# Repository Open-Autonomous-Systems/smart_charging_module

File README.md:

# smart_charging_module
open source hardware design and recorded software to be used for intelligently charge robotic platforms like UAVs, etc using low power energy sources. This repo contains ECAD source files and gerber file of the V1 of the project.

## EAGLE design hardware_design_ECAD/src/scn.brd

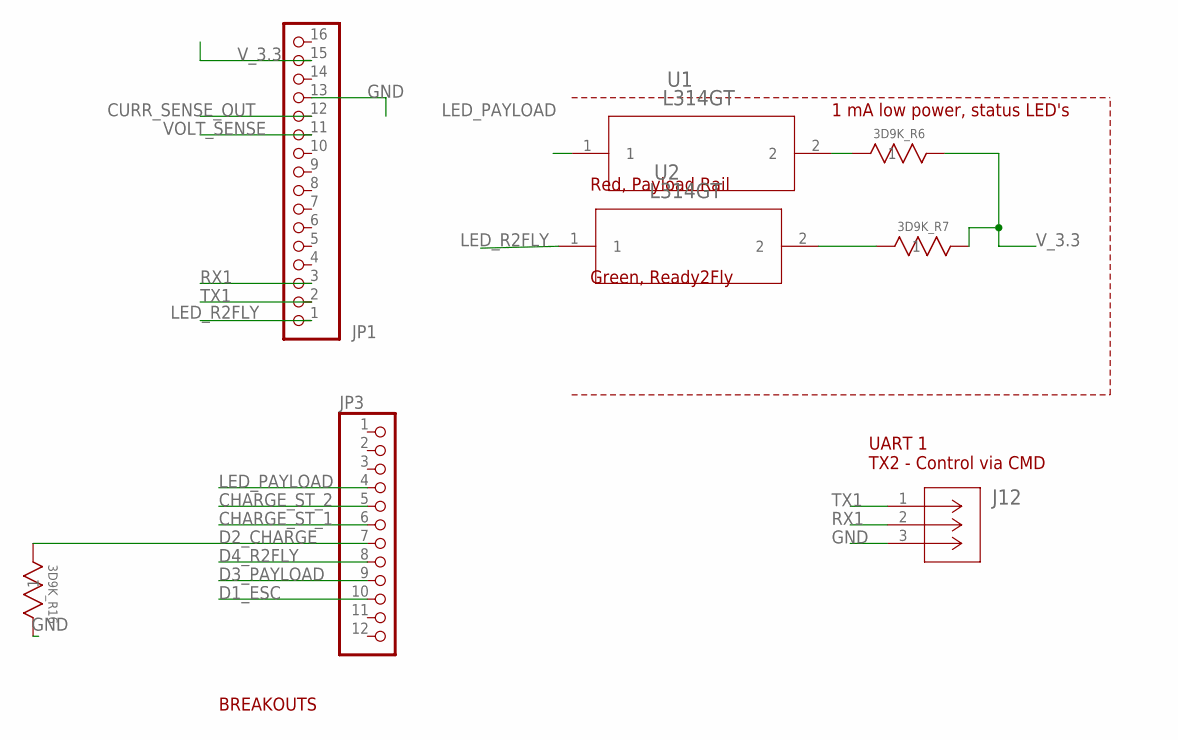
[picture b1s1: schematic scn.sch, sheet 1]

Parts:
3D9K_R6, 3D9K_R7, 3D9K_R16: CF14JT10K0; STA_CF14_STP
J12: B03B-PASK(LF)(SN); CONN_B03B-PASK_JST
JP1: HEADER-1X16ROUND; 1X16_ROUND
JP3: HEADER-1X12; 1X12_ROUND
U1, U2: L314GT; L314GT_AOP

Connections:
CHARGE_ST_1: JP3.6; also elsewhere on the board
CHARGE_ST_2: JP3.5; also elsewhere on the board
CURR_SENSE_OUT: JP1.12; also elsewhere on the board
D1_ESC: JP3.10; also elsewhere on the board
D2_CHARGE: 3D9K_R16.1, JP3.7; also elsewhere on the board
D3_PAYLOAD: JP3.9; also elsewhere on the board
D4_R2FLY: JP3.8
GND: 3D9K_R16.2, J12.3, JP1.13; also elsewhere on the board
LED_PAYLOAD: JP3.4, U1.1
LED_R2FLY: JP1.1, U2.1
unnamed: 3D9K_R6.1, U1.2
unnamed: 3D9K_R7.1, U2.2
RX1: J12.2, JP1.3
TX1: J12.1, JP1.2
VOLT_SENSE: JP1.11
V_3.3: 3D9K_R6.2, 3D9K_R7.2, JP1.15; also elsewhere on the board

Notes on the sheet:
BREAKOUTS
Red, Payload Rail
Green, Ready2Fly
1 mA low power, status LED's
UART 1 TX2 - Control via CMD

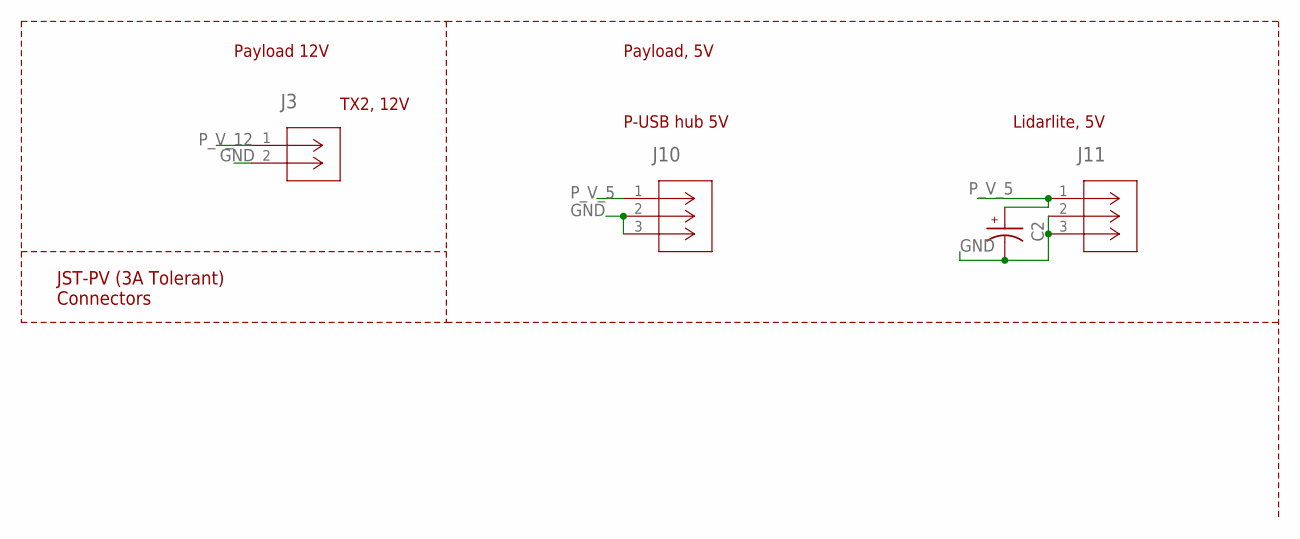
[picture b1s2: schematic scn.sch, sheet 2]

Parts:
C2: ECA1CM471; CAPPRD350W60D800H1150
J3: B02B-PASK(LF)(SN); CONN_B02B-PASK(LF)(SN)_JST
J10, J11: B03B-PASK(LF)(SN); CONN_B03B-PASK_JST

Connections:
GND: C2.N, J3.2, J10.2, J10.3, J11.2, J11.3; also elsewhere on the board
P_V_5: C2.P, J10.1, J11.1; also elsewhere on the board
P_V_12: J3.1; also elsewhere on the board

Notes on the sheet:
Payload 12V
Payload, 5V
TX2, 12V
Lidarlite, 5V
P-USB hub 5V
JST-PV (3A Tolerant) Connectors

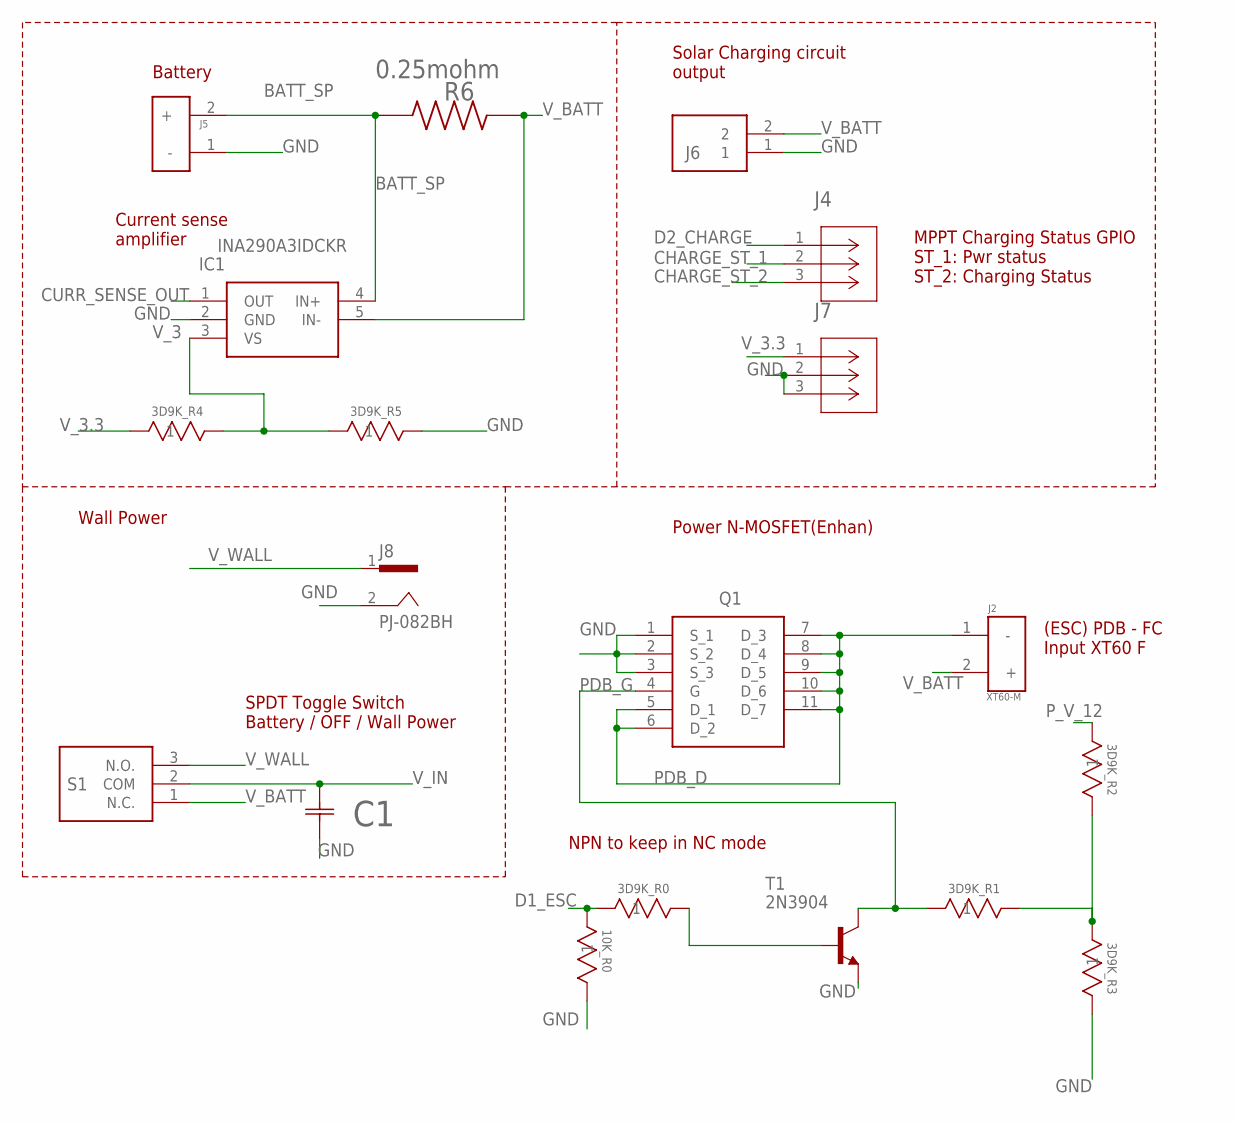
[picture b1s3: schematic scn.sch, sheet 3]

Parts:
3D9K_R0, 3D9K_R1, 3D9K_R2, 3D9K_R3, 3D9K_R4, 3D9K_R5, 10K_R0: CF14JT10K0; STA_CF14_STP
C1: 25PX1000MEFCT810X16; CAP_PK/PZ_10X16_LOW_RUB
IC1: INA290A3IDCKR; SOT65P210X110-5N
J2, J5: XT60-M; AMASS_XT60-M
J4, J7: B03B-PASK(LF)(SN); CONN_B03B-PASK_JST
J6: XT30UPB-M; SHDR2W160P0X500_1X2_1020X520X1
J8: PJ-082BH; CUI_PJ-082BH
Q1: SIRA50DP-T1-RE3; SI7852ADPT1GE3
R6: 0.25mohm; RESC6864X124N
S1: 48ASSP3S1M2QBT
T1: 2N3904; TO92

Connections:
BATT_SP: IC1.4 (IN+), J5.2 (+), R6.1
CHARGE_ST_1: J4.2; also elsewhere on the board
CHARGE_ST_2: J4.3; also elsewhere on the board
CURR_SENSE_OUT: IC1.1 (OUT); also elsewhere on the board
D1_ESC: 3D9K_R0.1, 10K_R0.1; also elsewhere on the board
D2_CHARGE: J4.1; also elsewhere on the board
GND: 3D9K_R3.2, 3D9K_R5.2, 10K_R0.2, C1.2, IC1.2 (GND), J5.1 (-), J6.1, J7.2, J7.3, J8.2, Q1.1 (S_1), Q1.2 (S_2), Q1.3 (S_3), T1.3 (E); also elsewhere on the board
unnamed: 3D9K_R1.2, 3D9K_R2.2, 3D9K_R3.1
unnamed: 3D9K_R0.2, T1.2 (B)
PDB_D: J2.1 (-), Q1.5 (D_1), Q1.6 (D_2), Q1.7 (D_3), Q1.8 (D_4), Q1.9 (D_5), Q1.10 (D_6), Q1.11 (D_7)
PDB_G: 3D9K_R1.1, Q1.4 (G), T1.1 (C)
P_V_12: 3D9K_R2.1; also elsewhere on the board
V_3: 3D9K_R4.2, 3D9K_R5.1, IC1.3 (VS)
V_3.3: 3D9K_R4.1, J7.1; also elsewhere on the board
V_BATT: IC1.5 (IN-), J2.2 (+), J6.2, R6.2, S1.1 (N.C.)
V_IN: C1.1, S1.2 (COM); also elsewhere on the board
V_WALL: J8.1, S1.3 (N.O.)

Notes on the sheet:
Current sense amplifier
Battery
Solar Charging circuit output
(ESC) PDB - FC Input XT60 F
Wall Power
SPDT Toggle Switch Battery / OFF / Wall Power
Power N-MOSFET(Enhan)
NPN to keep in NC mode
MPPT Charging Status GPIO ST_1: Pwr status ST_2: Charging Status

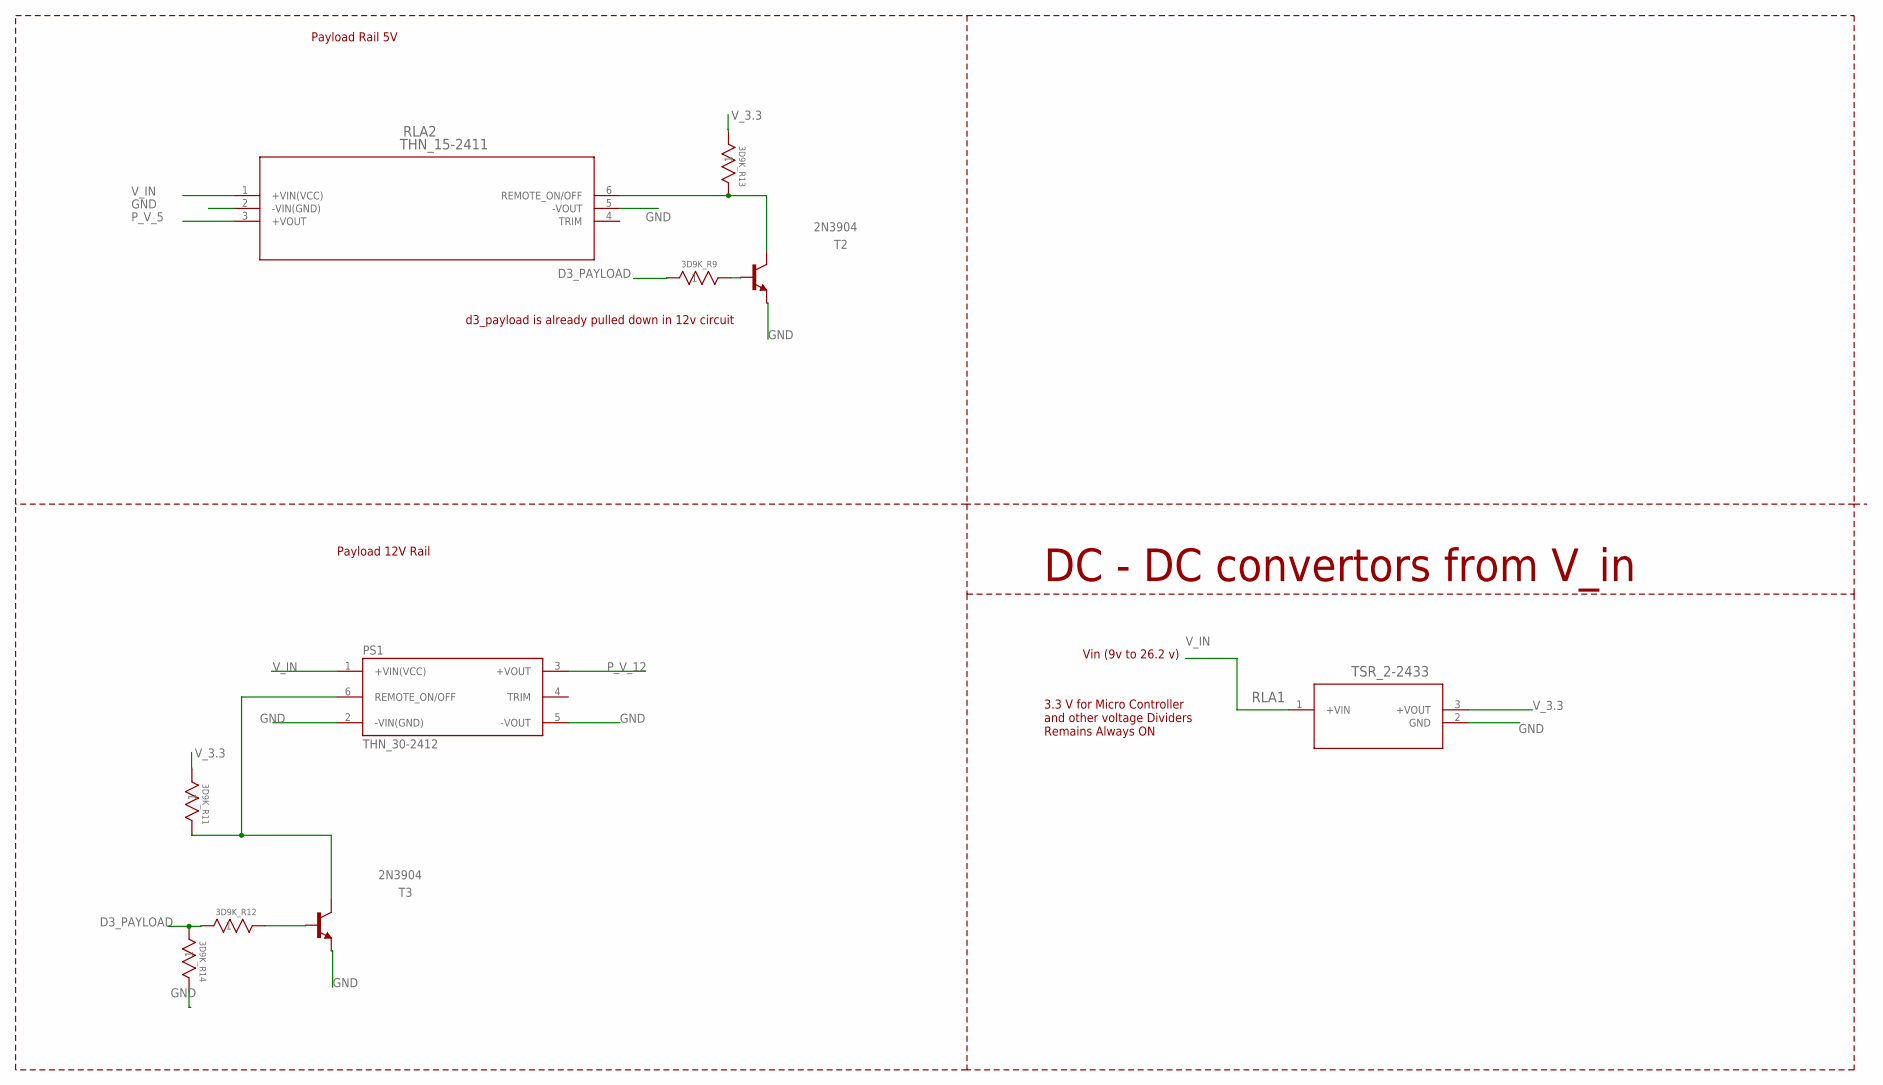
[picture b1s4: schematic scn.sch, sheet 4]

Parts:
3D9K_R9, 3D9K_R11, 3D9K_R12, 3D9K_R13, 3D9K_R14: CF14JT10K0; STA_CF14_STP
PS1: THN_30-2412; CONV_THN_30-2412
RLA1: TSR_2-2433; TSR2-SINGLE_TRP
RLA2: THN_15-2411; THN15-SINGLE_TRP
T2, T3: 2N3904; TO92

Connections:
D3_PAYLOAD: 3D9K_R9.1, 3D9K_R12.1, 3D9K_R14.1; also elsewhere on the board
GND: 3D9K_R14.2, PS1.2 (-VIN(GND)), PS1.5 (-VOUT), RLA1.2 (GND), RLA2.2 (-VIN(GND)), RLA2.5 (-VOUT), T2.3 (E), T3.3 (E); also elsewhere on the board
unnamed: 3D9K_R13.2, RLA2.6 (REMOTE_ON/OFF), T2.1 (C)
unnamed: 3D9K_R9.2, T2.2 (B)
unnamed: 3D9K_R12.2, T3.2 (B)
unnamed: 3D9K_R11.2, PS1.6 (REMOTE_ON/OFF), T3.1 (C)
P_V_5: RLA2.3 (+VOUT); also elsewhere on the board
P_V_12: PS1.3 (+VOUT); also elsewhere on the board
V_3.3: 3D9K_R11.1, 3D9K_R13.1, RLA1.3 (+VOUT); also elsewhere on the board
V_IN: PS1.1 (+VIN(VCC)), RLA1.1 (+VIN), RLA2.1 (+VIN(VCC)); also elsewhere on the board

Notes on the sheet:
Payload Rail 5V
Vin (9v to 26.2 v)
DC - DC convertors from V_in
3.3 V for Micro Controller and other voltage Dividers Remains Always ON
Payload 12V Rail
d3_payload is already pulled down in 12v circuit

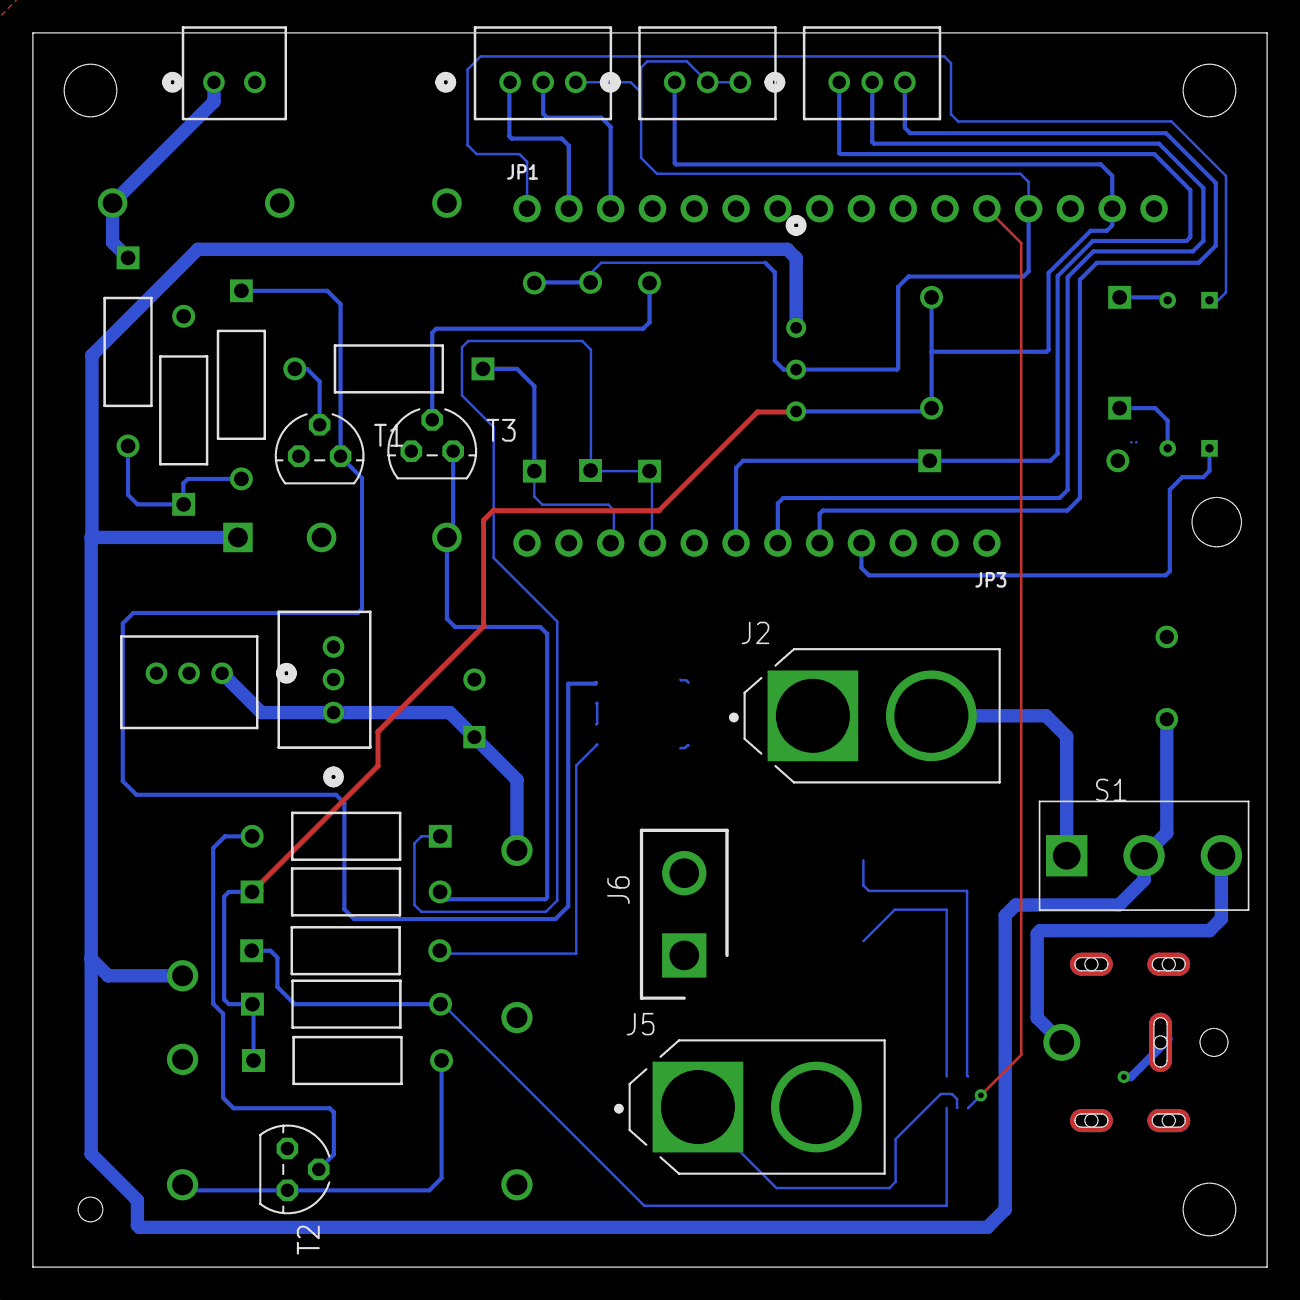
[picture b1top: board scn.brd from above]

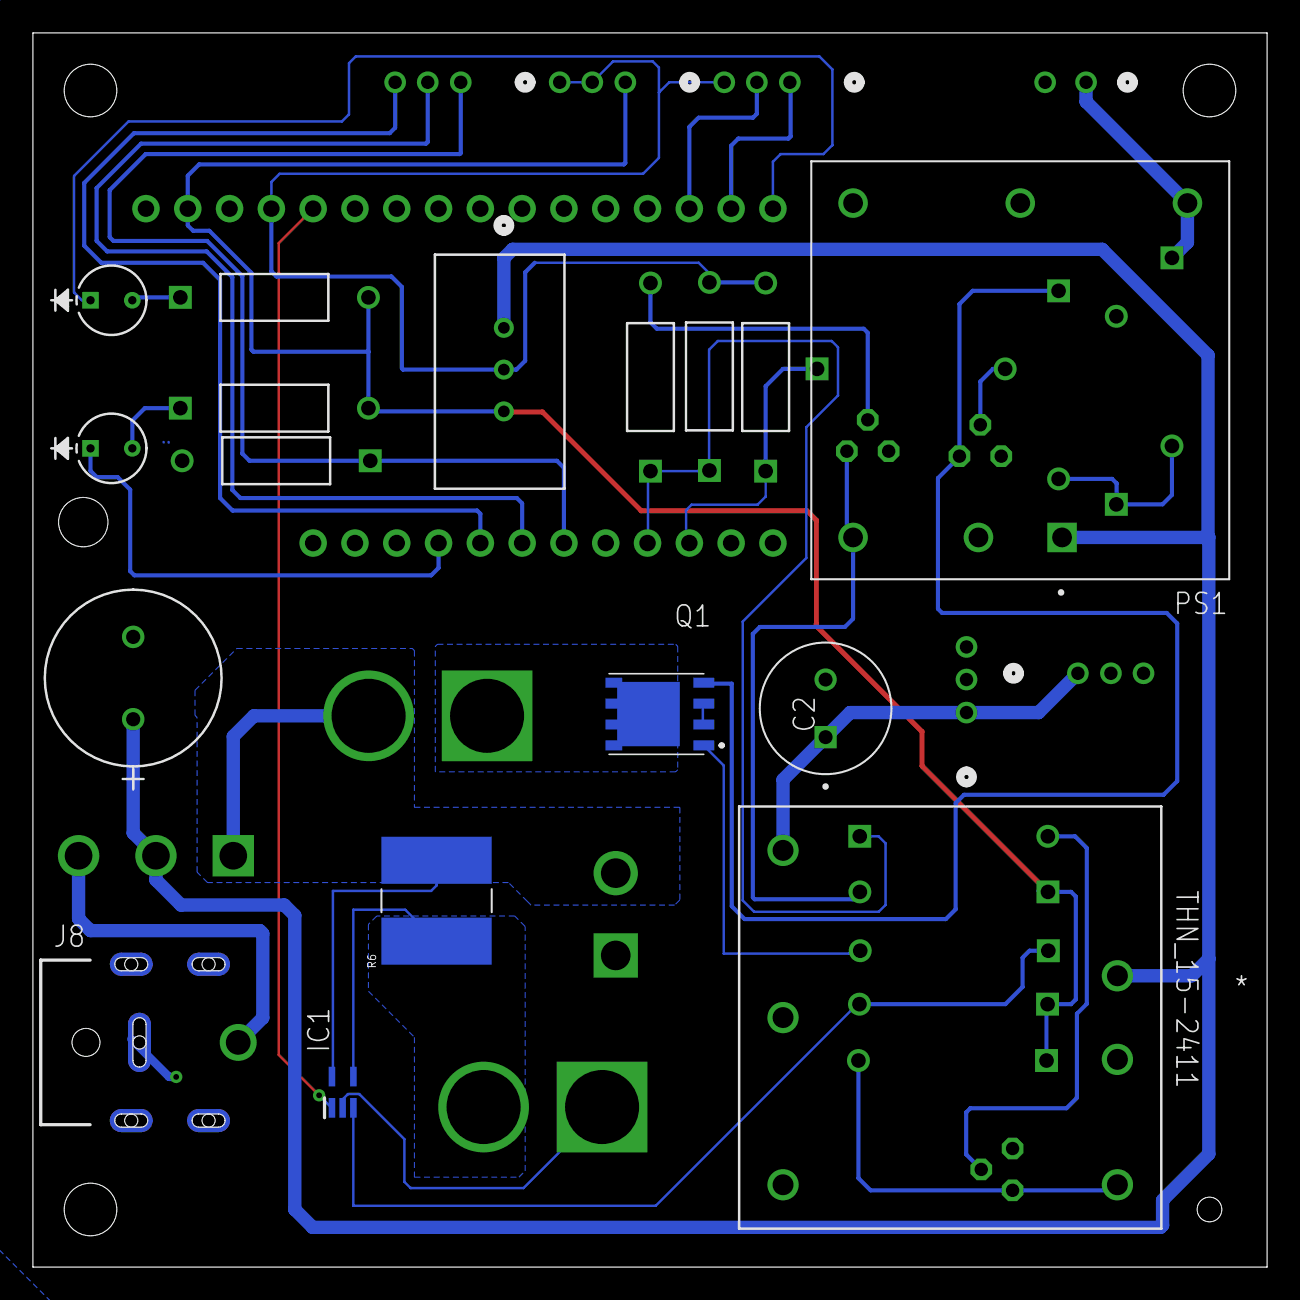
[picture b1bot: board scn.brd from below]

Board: 2 copper layers, 75.0 x 75.0 mm, 41 parts (17 on the bottom side), 29 nets.

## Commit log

2023-08-22 (CHORE) - (INIT) - push to public git as init commit

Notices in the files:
parts and their libraries:
microbuilder: This work is placed in the public domain, and may be freely used for commercial and non-commercial work with the following conditions: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
COPYRIGHT: Copyright (C) 2022 Ultra Librarian. All rights reserved.
COPYRIGHT: Copyright (C) 2018 Accelerated Designs. All rights reserved
